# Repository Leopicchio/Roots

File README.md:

# Roots

<p float="left">

</p>

Welcome to the Roots project! 

We created a touch sensor which is capable of recognizing complex interactions with everyday objects, only through a single wire connection. Our sensor measures the electrical property of the object over a range of frequencies and sends the data to a remote device (for example a laptop) via Wifi. The data is analyzed with a simple machine learning technique to recognize where and how we are touching the object.

We designed everything from scratch, starting with the PCB and ending with the classification algorithm and the user interface (which was written with the Qt framework). We then tested our sensor with different conductive objects like plants, earphones or lamps and we were able to recognize where and how the person is touching the object!

here is a link with a possible case scenario for our sensor
https://www.youtube.com/watch?v=_SN1TQER2w4&ab_channel=A.Bricq

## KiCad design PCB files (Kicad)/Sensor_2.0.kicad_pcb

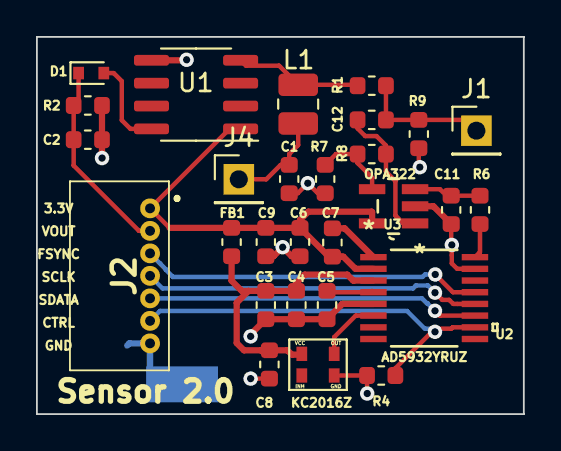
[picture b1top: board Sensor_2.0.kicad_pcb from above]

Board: 2 copper layers, 27.1 x 21.0 mm, 29 parts (1 on the bottom side), 20 nets.

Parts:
C1: 10p; C_0603_1608Metric
C2: 1u; C_0603_1608Metric
C3, C5, C8, C9: 100nF; C_0603_1608Metric
C4, C6: 10uF; C_0603_1608Metric
C7: 10nF; C_0603_1608Metric
C11: 200p; C_0603_1608Metric
C12: 320p; C_0603_1608Metric
D1: 1N914; D_SOD-523
FB1: Ferrite_Bead; L_0603_1608Metric
J1, J4: Conn_01x01_Male; PinHeader_1x01_P2.54mm_Vertical
J2: 0530480710
L1: 1m; L_1008_2520Metric
NT1: Net-Tie_2; NetTie-2_SMD_Pad2.0mm
R1: 1k; R_0603_1608Metric
R2: 10M; R_0603_1608Metric
R4: 10k; R_0603_1608Metric
R6: 100; R_0603_1608Metric
R7: 2k; R_0603_1608Metric
R8: 6k; R_0603_1608Metric
R9: 100k; R_0603_1608Metric
U1: BUF602xD; SOIC-8_3.9x4.9mm_P1.27mm
U2: AD5932YRUZ
U3: OPA322; OPA322AIDBVR
U4: KC2016Z

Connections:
+3V3: C6.1, C7.2, C9.1, FB1.1, J2.1, U1.1, U2.2, U3.5
CTRL: J2.6, R4.1, U2.10
DVDD: C3.2, C4.2, C8.2, FB1.2, U2.3, U4.4
ELECTRODE: C1.1, J4.1, L1.2
FSYNC: J2.3, U2.13
GNDA: C1.2, C2.2, C6.2, C9.2, C11.2, J2.7, NT1.1, R2.2, R7.2, R9.2, U1.5, U2.15, U3.2
GNDD: C3.1, C4.1, C5.2, C8.1, NT1.2, R4.2, U2.5, U4.2
MCLK: U2.6, U4.3
unnamed: C5.1, U2.4
unnamed: C7.1, U2.1
unnamed: C11.1, R6.1, U3.3
unnamed: C12.1, J1.1, R1.2, R9.1
unnamed: C12.2, R8.1, U3.1
unnamed: D1.2, U1.8
unnamed: L1.1, R1.1, U1.4
unnamed: R7.1, R8.2, U3.4
SCLK: J2.4, U2.12
SDATA: J2.5, U2.11
SIGNAL: R6.2, U2.16
VOUT: C2.1, D1.1, J2.2, R2.1

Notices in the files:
parts and their libraries:
Copyright 2016 Accelerated Designs. All rights reserved.
